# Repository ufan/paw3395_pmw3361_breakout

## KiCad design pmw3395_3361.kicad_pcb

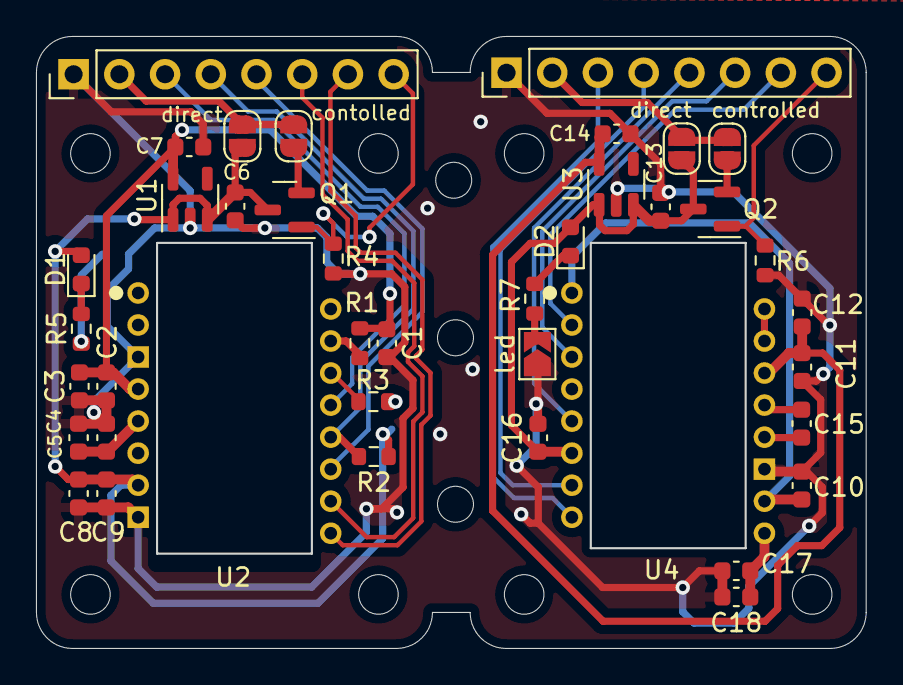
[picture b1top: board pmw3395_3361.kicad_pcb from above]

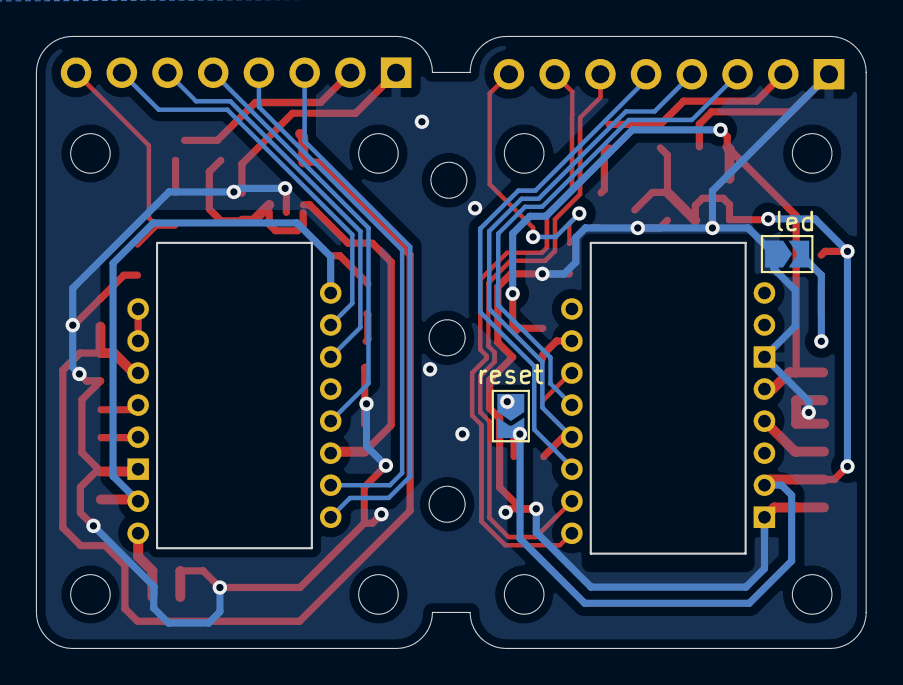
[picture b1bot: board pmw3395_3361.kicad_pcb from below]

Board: 2 copper layers, 46.0 x 33.9 mm, 42 parts (2 on the bottom side), 34 nets.

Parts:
C1: 33u; C_0603_1608Metric
C2, C4, C6, C8, C13: 0.1u; C_0603_1608Metric
C3, C9: 10u; C_0603_1608Metric
C5: 4.7u; C_0603_1608Metric
C7, C14: 1u; C_0603_1608Metric
C10: 10n; C_0603_1608Metric
C11, C16: 100n; C_0603_1608Metric
C12: 3.3u/16V; C_0603_1608Metric
C15: 100n (X7R); C_0603_1608Metric
C17: 10u (X7R); C_0603_1608Metric
C18: 10n (X7R); C_0603_1608Metric
D1, D2: Orange; LED_0603_1608Metric
J1, J2: Conn_01x08; PinHeader_1x08_P2.54mm_Vertical
Q1, Q2: AO3401A; SOT-23
R1: 5.6; R_0603_1608Metric
R2: 10k; R_0603_1608Metric
R3, R4, R6: 2M; R_0603_1608Metric
R5, R7: 100; R_0603_1608Metric
U1, U3: TCR2EF19; SOT-23-5
U2: PAW3395
U4: PMW3610
contolled: SolderJumper_2_Open; SolderJumper-2_P1.3mm_Open_RoundedPad1.0x1.5mm
controlled: SolderJumper_2_Open; SolderJumper-2_P1.3mm_Open_RoundedPad1.0x1.5mm
direct: SolderJumper_2_Open; SolderJumper-2_P1.3mm_Open_RoundedPad1.0x1.5mm
direct#2: SolderJumper_2_Open; SolderJumper-2_P1.3mm_Open_RoundedPad1.0x1.5mm
led: SolderJumper_2_Open; SolderJumper-2_P1.3mm_Open_TrianglePad1.0x1.5mm
led#2: SolderJumper_2_Open; SolderJumper-2_P1.3mm_Open_TrianglePad1.0x1.5mm
reset: SolderJumper_2_Open; SolderJumper-2_P1.3mm_Open_TrianglePad1.0x1.5mm

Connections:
+1V8: C1.1, C2.1, C3.1, C7.1, R1.1, U1.5 (OUT), U2.4 (VDD)
+1V9: C11.1, C12.1, C14.1, U3.5 (OUT), U4.14 (VDD)
+3.3VA: C6.2, C8.1, C9.1, D1.2 (A), Q1.3 (D), R2.1, U1.1 (IN), U1.3 (EN), U2.7 (VDDIO), direct.2 (B), reset.2 (B)
+3V3: J1.2, contolled.1 (A), direct.1 (A)
+3V3_CUT: J1.8, Q1.1 (G), R4.2
GND: C1.2, C2.2, C3.2, C4.2, C5.2, C6.1, C7.2, C8.2, C9.2, C10.2, C11.2, C12.2, C13.1, C14.2, C16.2, C17.2, C18.2, J1.1, J2.1, R4.1, R6.1, U1.2 (GND), U2.3 (GND), U2.8 (GNDIO), U3.2 (GND), U4.11 (GND), led.1 (A), led#2.1 (A)
MISO: J1.4, R2.2, U2.12 (MISO)
MOSI: J1.5, U2.11 (MOSI)
MOTION: J1.7, U2.9 (MOTION)
MOTION_2: J2.3, U4.8 (MOTION)
NCS: J1.3, U2.13 (NCS)
NCS_2: J2.5, U4.5 (NCS)
unnamed: C4.1, C5.1, U2.5 (VDDREG)
unnamed: C10.1, U4.1 (+VCSEL), U4.10 (PASS_T)
unnamed: C15.1, U4.13 (CN)
unnamed: C15.2, U4.12 (CP)
unnamed: C17.1, C18.1, U4.9 (VCP)
unnamed: D1.1 (K), R5.1
unnamed: D2.1 (K), R7.1
unnamed: R3.1, reset.1 (A)
unnamed: R5.2, led#2.2 (B)
unnamed: Q1.2 (S), contolled.2 (B)
unnamed: R7.2, led.2 (B)
unnamed: Q2.2 (S), controlled.2 (B)
unnamed: R1.2, U2.15 (LED_P)
unnamed: R3.2, U2.14 (NRESET)
unnamed: U4.15 (XYLASER), U4.16 (-VCSEL)
RESET_2: J2.4, U4.7 (NRESET)
SCLK: J1.6, U2.10 (SCLK)
SCLK_2: J2.6, U4.3 (SCLK)
SDIO_2: J2.7, U4.2 (SDIO)
VCC: J2.2, controlled.1 (A), direct#2.1 (A)
VCC_CUT: J2.8, Q2.1 (G), R6.2
VCC_OUT: C13.2, C16.1, D2.2 (A), Q2.3 (D), U3.1 (IN), U3.3 (EN), U4.6 (VDDIO), direct#2.2 (B)

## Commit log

2022-08-20 [v0.99] initial verion with two connected breakout boards
    for paw3395 and pmw3361 respectively
2022-08-31 bugfix
    enlarge pmw3395 edge cut, the dimension given in the datasheet is
    smaller than actual size. The same for pmw3360
